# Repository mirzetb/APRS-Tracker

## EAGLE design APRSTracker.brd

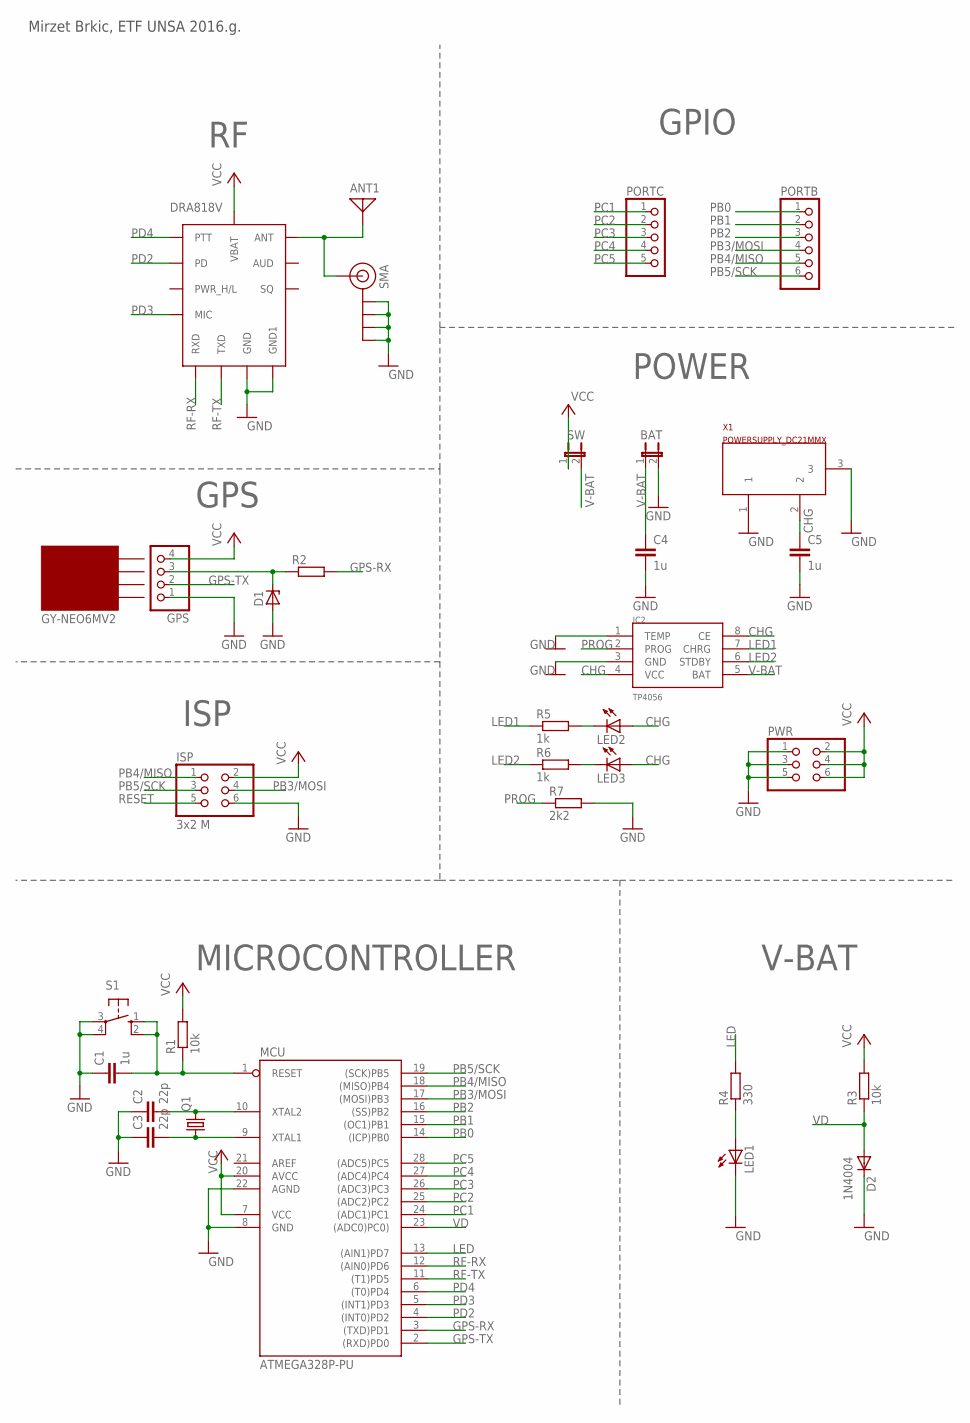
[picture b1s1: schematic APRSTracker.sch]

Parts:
ANT1: ANTENNA; PAD-01
BAT: JP1E; JP1
C1, C4, C5: 1u; C050-024X044
C2, C3: 22p; C025-024X044
D1: ZENER-DIODEDO35Z10; DO35Z10
D2: 1N4004; DO41-10
DRA818V: DRA818V; DRA8XXZ
GPS: PINHD-1X4; 1X04
IC2: TP4056; SOP-8
ISP: 3x2 M; 2X03
LED1, LED2, LED3: LED3MM
MCU: ATMEGA328P-PU; DIL28-3
PORTB: PINHD-1X6; 1X06
PORTC: PINHD-1X5; 1X05
PWR: PINHD-2X3; 2X03
Q1: CRYSTALHC49S; HC49/S
R1, R3: 10k; 0207/10
R2: R-EU_0207/10; 0207/10
R4: 330; 0207/10
R5, R6: 1k; 0207/10
R7: 2k2; 0207/10
S1: 10-XX; B3F-10XX
SMA: SMA_EDGE; SMA-EDGE
SW: JP1E; JP1
X1: POWERSUPPLY_DC21MMX; POWERSUPPLY_DC-21MM

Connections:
CHG: C5.1, IC2.4 (VCC), IC2.8 (CE), LED2.A, LED3.A, X1.2
GND: BAT.2, C1.1, C2.1, C3.1, C4.2, C5.2, D1.A, D2.C, DRA818V.P$9 (GND), DRA818V.P$10 (GND1), GPS.1, IC2.1 (TEMP), IC2.3 (GND), ISP.6, LED1.K (C), MCU.8 (GND), MCU.22 (AGND), PWR.1, PWR.3, PWR.5, R7.2, S1.3, S1.4 (P1), SMA.GND@0 (GND), SMA.GND@1 (GND), SMA.GND@2 (GND), SMA.GND@3 (GND), X1.1, X1.3
GPS-RX: MCU.3 ((TXD)PD1), R2.2
GPS-TX: GPS.2, MCU.2 ((RXD)PD0)
LED: MCU.13 ((AIN1)PD7), R4.2
LED1: IC2.7 (CHRG), R5.1
LED2: IC2.6 (STDBY), R6.1
unnamed: ANT1.1, DRA818V.P$12 (ANT), SMA.SIG (SIGNAL)
unnamed: D1.C, GPS.3, R2.1
unnamed: LED1.A, R4.1
unnamed: LED2.K (C), R5.2
unnamed: C3.2, MCU.9 (XTAL1), Q1.1
unnamed: C2.2, MCU.10 (XTAL2), Q1.2
unnamed: LED3.K (C), R6.2
PB0: MCU.14 ((ICP)PB0), PORTB.1
PB1: MCU.15 ((OC1)PB1), PORTB.2
PB2: MCU.16 ((SS)PB2), PORTB.3
PB3/MOSI: ISP.4, MCU.17 ((MOSI)PB3), PORTB.4
PB4/MISO: ISP.1, MCU.18 ((MISO)PB4), PORTB.5
PB5/SCK: ISP.3, MCU.19 ((SCK)PB5), PORTB.6
PC1: MCU.24 ((ADC1)PC1), PORTC.1
PC2: MCU.25 ((ADC2)PC2), PORTC.2
PC3: MCU.26 ((ADC3)PC3), PORTC.3
PC4: MCU.27 ((ADC4)PC4), PORTC.4
PC5: MCU.28 ((ADC5)PC5), PORTC.5
PD2: DRA818V.P$6 (PD), MCU.4 ((INT0)PD2)
PD3: DRA818V.P$18 (MIC), MCU.5 ((INT1)PD3)
PD4: DRA818V.P$5 (PTT), MCU.6 ((T0)PD4)
PROG: IC2.2 (PROG), R7.1
RESET: C1.2, ISP.5, MCU.1 (RESET), R1.1, S1.1 (S), S1.2 (S1)
RF-RX: DRA818V.P$16 (RXD), MCU.12 ((AIN0)PD6)
RF-TX: DRA818V.P$17 (TXD), MCU.11 ((T1)PD5)
V-BAT: BAT.1, C4.1, IC2.5 (BAT), SW.2
VCC: DRA818V.P$8 (VBAT), GPS.4, ISP.2, MCU.7 (VCC), MCU.20 (AVCC), PWR.2, PWR.4, PWR.6, R1.2, R3.2, SW.1
VD: D2.A, MCU.23 ((ADC0)PC0)), R3.1

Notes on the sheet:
GPIO
GPS
POWER
ISP
V-BAT
MICROCONTROLLER
SMA
Mirzet Brkic, ETF UNSA 2016.g.
GY-NEO6MV2

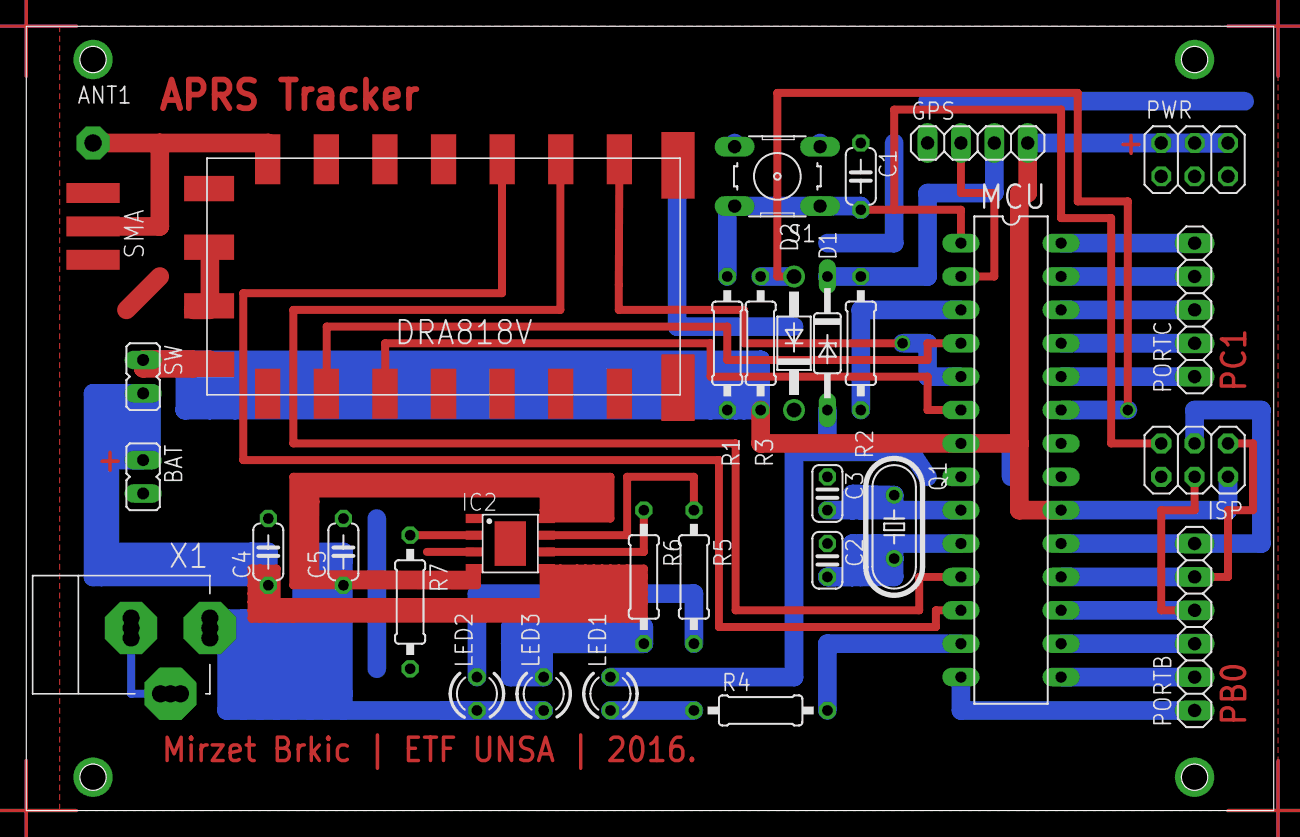
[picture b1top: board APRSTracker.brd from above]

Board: 2 copper layers, 94.9 x 59.7 mm, 32 parts (0 on the bottom side), 35 nets.

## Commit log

2016-06-16 shema v1
2016-06-17 inicijalni doc
2016-07-23 sch update
2016-07-31 shema v2
2016-07-31 code init - trackuino
2016-08-01 brd v1
2016-08-01 brd update
2016-08-11 uvod
2016-08-11 .doc del
2016-08-11 bell 202
2016-08-12 AX.25
2016-08-14 simboli + mreza
2016-08-14 rutiranje
2016-08-16 fcs, beacon, packet timing
2016-08-21 arhitektura
2016-08-21 arduino
2016-08-22 rf modul
2016-08-23 power
2016-08-23 gpio + isp
2016-08-23 pcb dizajn + zakljucak 2
2016-09-07 code v2
2016-09-07 sch & brd update
2016-09-18 final
2016-09-21 final v2
